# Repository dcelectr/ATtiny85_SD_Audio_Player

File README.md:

# ATtiny85_SD_Audio_Player
Based on [Simple SD Audio Player](http://elm-chan.org/works/sd8p/report.html)
High voltage serial programer is needed to set the RSTDISBL fuse for the ATiny SD Audio Player (Stereo, OSC, and Mono-HR versions).
You may used the [ProMini HVSP](https://github.com/dcelectr/ProMini_HVSP/tree/main)

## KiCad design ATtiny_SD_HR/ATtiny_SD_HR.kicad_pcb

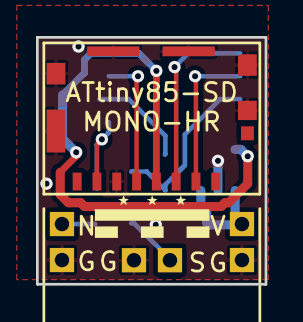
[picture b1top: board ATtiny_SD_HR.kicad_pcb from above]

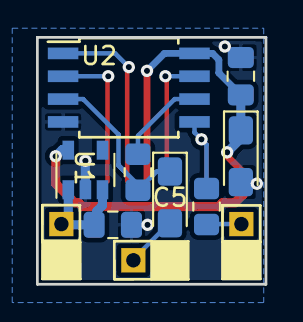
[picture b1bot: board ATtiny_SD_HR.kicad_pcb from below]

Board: 2 copper layers, 12.7 x 13.7 mm, 12 parts (11 on the bottom side), 11 nets.

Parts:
C1, C3: 100nF; C_0805_2012Metric_Pad1.18x1.45mm_HandSolder
C2: 150uF; CP_EIA-3216-10_Kemet-I_Pad1.58x1.35mm_HandSolder
C5: 100uF; CP_EIA-3216-10_Kemet-I_Pad1.58x1.35mm_HandSolder
J1: Micro_SD_Card_Det; Molex_1051620001_KiCad
J2, J3, J4: Conn_01x02_Male; PinHeader_1x02_P2.00mm_Vertical
R1: 4.7K; R_0805_2012Metric_Pad1.20x1.40mm_HandSolder
R2: 4.5K; R_0805_2012Metric_Pad1.20x1.40mm_HandSolder
U1: AP2112K-3.3; SOT-23-5
U2: ATtiny85-20SU; SOIC-8W_5.3x5.3mm_P1.27mm

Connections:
/CS: J1.2, U2.2
/MISO: J1.7, R1.2, U2.5
/MOSI: J1.3, U2.1
/NEXT: J3.1, R1.1
/SCLK: J1.5, U2.7
/SOUND: C5.2, J4.1
GND: C1.2, C2.2, C3.2, J1.6, J1.10, J1.11, J2.2, J3.2, J4.2, U1.2, U2.4
unnamed: C5.1, R2.2, U2.3
unnamed: R2.1, U2.6
VBUS: C1.1, J2.1, U1.1, U1.3
VCC: C2.1, C3.1, J1.4, U1.5, U2.8

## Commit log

2021-04-01 Initial Upload
